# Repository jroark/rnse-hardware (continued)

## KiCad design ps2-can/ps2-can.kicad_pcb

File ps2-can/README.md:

# RNS-E PS/2 to CAN adapter — revision A

Open **ps2-can.kicad_pro** in KiCad 10. This project contains an editable schematic,
a 65 × 45 mm two-layer PCB and local libraries. All parts mount on the top side.
The design is a prototype: it has not been fabricated or electrically tested.
Adapter firmware and the RNS-E Linux CAN/input driver are not included.

## Connections

| Connector | Pin | Signal |
|---|---|---|
| J1 vehicle, numbered square pad first | 1 | Switched +12 V |
| J1 | 2 | Ground |
| J1 | 3 | Infotainment CANH |
| J1 | 4 | Infotainment CANL |
| J2 keyboard / J3 mouse | 1 | PS/2 data |
| J2 / J3 | 2, 6 | Unconnected |
| J2 / J3 | 3 | Ground |
| J2 / J3 | 4 | Individually fused +5 V |
| J2 / J3 | 5 | PS/2 clock |
| J4 UPDI | 1 | +5 V target voltage reference |
| J4 | 2 | UPDI / PA0 |
| J4 | 3 | Ground |

J4 is a **5 V UPDI** connection. Power the target from J1; configure the programmer
to sense target voltage without supplying it. Preserve PA0's UPDI fuse setting.
The peripheral sockets are for genuine PS/2 devices; passive USB adapters require
peripherals that explicitly support PS/2. Connect peripherals with power off.
The board shares ground with the vehicle; it is not isolated.

## Ordering

Use [the current stock update](ordering/stock-update.md) for revised headerless
DigiKey and Mouser orders. The base [distributor order files](ordering/README.md)
record the design-MPN baseline for one-board DigiKey or
Mouser upload. They group the BOM into 24 lines / 48 components, excluding bare
test pads. The checked BOM corrects the F1 fuse and Y1 crystal package selections
and uses an orderable Vishay SS16 for D1; the existing PCB fits these parts.

## Assembly

Use `bom.csv` for exact MPNs and search links; `previews/assembly.pdf` identifies
parts. Purchase MD-60S sockets made **after 2022-03-03**. Earlier versions have
different hole spacing. The custom footprint follows the current top-view drawing:
pins 4/2/1/3 at x = -3.4/-1.3/+1.3/+3.4 mm, y = 8.5 mm from the front;
pins 6/5 at x = -3.4/+3.4 mm, y = 11 mm; locating slot 2.2 × 0.7 mm at y = 4.7 mm.
Confirm the supplied socket against a 1:1 print before soldering.

Fit resistors/capacitors and SOIC devices first, then power protection, LEDs,
crystal, regulator and connectors. Use flux and an ordinary fine soldering tip.
The SOD-323 ESD diodes are the smallest parts; they have exposed terminals and
are bidirectional, so either orientation works. D1/D2 and LEDs are polarized:
follow the cathode marks and assembly drawing. SOIC pin 1 uses the dot/notch.
TP1–TP4 are bare plated holes, not purchased components. H1–H4 accept M2 hardware.
Allow clearance under the board for the mini-DIN locating tabs and solder joints.

## Power and CAN design

J1 input passes through a 0.5 A fuse and SS16 reverse-polarity diode. SMBJ18A
clamps the protected VBAT rail. TSR 1-2450 converts it to 5 V with a 1 A rating.
Input operation is nominally 9–16 V; brownout/reset during cranking is acceptable.
C5 is rated 50 V; the regulator input limit is 36 V and TJA1055 BAT limit is 40 V.
The TVS nominal maximum clamp is 29.2 V at its specified pulse current, below both
limits. This comparison does not establish load-dump immunity: fuse opening time,
TVS energy, source impedance and wiring overshoot need physical testing. Do not
use a continuously applied supply above the TVS stand-off rating.

Each PS/2 port has a 0.20 A hold PTC (temperature dependent). Budget 100 mA each
for keyboard and mouse and approximately 100 mA for board/CAN operation. The
regulator has margin for startup and CAN activity, but these ports are not intended
for illuminated high-current peripherals. Routing uses 0.25 mm tracks with 0.1874 mm fanout sections,
0.20 mm clearances and 0.6/0.3 mm vias. The project minimum trace width is 0.15 mm;
see the PCB width audit for actual widths. Both copper layers have grounded pours; no assumption of automotive EMC
qualification is made.

The bus interface is **TJA1055T**, fault-tolerant ISO 11898-3. A TJA1051, MCP2551,
SN65HVD230 or conventional high-speed CAN module is not a substitute. The MCP2515
is the CAN protocol controller; its 16 MHz crystal supplies the accurate CAN clock.
The AVR uses its internal clock. No CAN FD is used.

R13/R14 provide distributed termination to TJA1055 RTH/RTL, initially 5.6 kΩ each.
They are not a 120 Ω termination across CANH/CANL. NXP recommends a whole-network
effective termination of approximately 100 Ω per line; actual node resistors and
network topology determine the result. The fitted values minimally load an
existing vehicle network. For a small bench network, inspect the other node's
termination and select an appropriate pair (within the manufacturer's limits),
then verify bus levels and error counters. Do not expect a two-node bench with
two 5.6 kΩ terminations to represent a correctly terminated vehicle network.

CAN EN/STB have pull-downs, so the board powers up in standby. TXD has a pull-up;
MCP2515 CS and RESET are pulled high. INH is intentionally unconnected. WAKE is
held to protected VBAT through 10 kΩ. This revision uses switched power; it does
not implement an always-on wake/power manager.

## Firmware interfaces and bring-up

See `firmware-interface.md` for the pin allocation and proposed wire protocol.
The Linux configuration in this repository has evdev but no networking; CAN and
input integration are additional work, not provided by this circuit.

1. Inspect soldering and resistance between VBAT/5 V and ground with power off.
2. With peripherals and vehicle CAN disconnected, apply a current-limited 12 V
   bench supply (start at 100 mA). Check VBAT polarity, 5 V regulation and POWER LED.
3. Attach a 5 V UPDI programmer to J4. Read device identity before programming.
   Start with transceiver EN/STB low; check both with a meter or logic analyzer.
4. Test each PS/2 device separately. Verify idle-high clock/data, reset/BAT exchange,
   open-drain host signaling and independent port fuses. Increase supply current
   limit only as required for the measured peripheral load.
5. Test MCP2515 SPI identity/configuration and internal loopback before enabling
   the transceiver. Check oscillator startup and the selected CAN timing.
6. Connect a correctly terminated **fault-tolerant** CAN bench node and a common
   ground. Start with receive-only operation. Verify ACKs, error counters, bus
   voltage levels and 100 kbit/s timing before transmitting test input packets.
7. Validate CAN identifiers against the actual vehicle network before installation.
   Use bounded packet rates and disable transmission on bus-off or firmware faults.
8. Before any RNS-E hardware test payload is delivered, verify the actual physical
   display-open motor command and separate disc-eject command on normal/error
   screens and during reads/initialization. Keep polling responsive and audit any
   loader/updater handoff. A reset, return shortcut or displayed eject button is
   not proof of physical ejection. This PCB does not replace that control path.

## Files and reproduction

- `ps2-can.kicad_sch`, `.kicad_pcb`, `.kicad_pro`: editable source.
- `ps2-can.kicad_sym`, `ps2-can.pretty/`, library tables: local symbols/footprints.
- `bom.csv`, `connectivity.json`: purchase list and reference connectivity/placement.
- `previews/`: schematic, assembly and board previews.
- `manufacturing/`: Gerbers and Excellon drills for 2 layers, 1.6 mm FR-4, 1 oz copper.
- `reports/`: ERC, DRC, exported schematic netlist and connectivity/width audits.
- `generate.py`: regenerates schematic and **unrouted** PCB; overwrites manual edits.
- `ps2-can.dsn`, `final.ses`: Specctra interchange for the final route.

Generation uses KiCad's bundled Python with `pcbnew`. Route the DSN with
Freerouting 2.5.0, fanout enabled, automatic neckdown disabled and optimization
disabled; the final session routes every connection. Export the schematic XML
netlist to `reports/schematic.xml` before finishing the board. `finish.py` imports the resulting session and fills the ground
zones. Run `label-board.py` once to place the silkscreen legends, then run checks/export again after any change; do not reuse stale Gerbers.
Project symbols deliberately show actual pin numbers and explicit net labels.

## Manufacturer references

- [ATtiny1616 datasheet](https://ww1.microchip.com/downloads/aemDocuments/documents/MCU08/ProductDocuments/DataSheets/ATtiny1614-16-17-DataSheet-DS40002204A.pdf)
- [MCP2515 datasheet](https://ww1.microchip.com/downloads/en/DeviceDoc/MCP2515-Stand-Alone-CAN-Controller-with-SPI-20001801J.pdf)
- [TJA1055 datasheet](https://www.nxp.com/docs/en/data-sheet/TJA1055.pdf) and [application guidance](https://www.nxp.com/docs/en/application-note/AH0801.pdf)
- [MD-S socket drawing, page 3](https://www.sameskydevices.com/product/resource/md-s.pdf)
- [TSR 1 regulator datasheet](https://www.tracopower.com/sites/default/files/products/datasheets/tsr1_datasheet.pdf)
- [PESD5V0S1BA datasheet](https://assets.nexperia.com/documents/data-sheet/PESD5V0S1BA.pdf)

KiCad-derived local footprints retain their original library provenance and are
covered by the KiCad libraries' CC BY-SA 4.0 license with their exception for
commercial PCB fabrication. No third-party firmware is included.

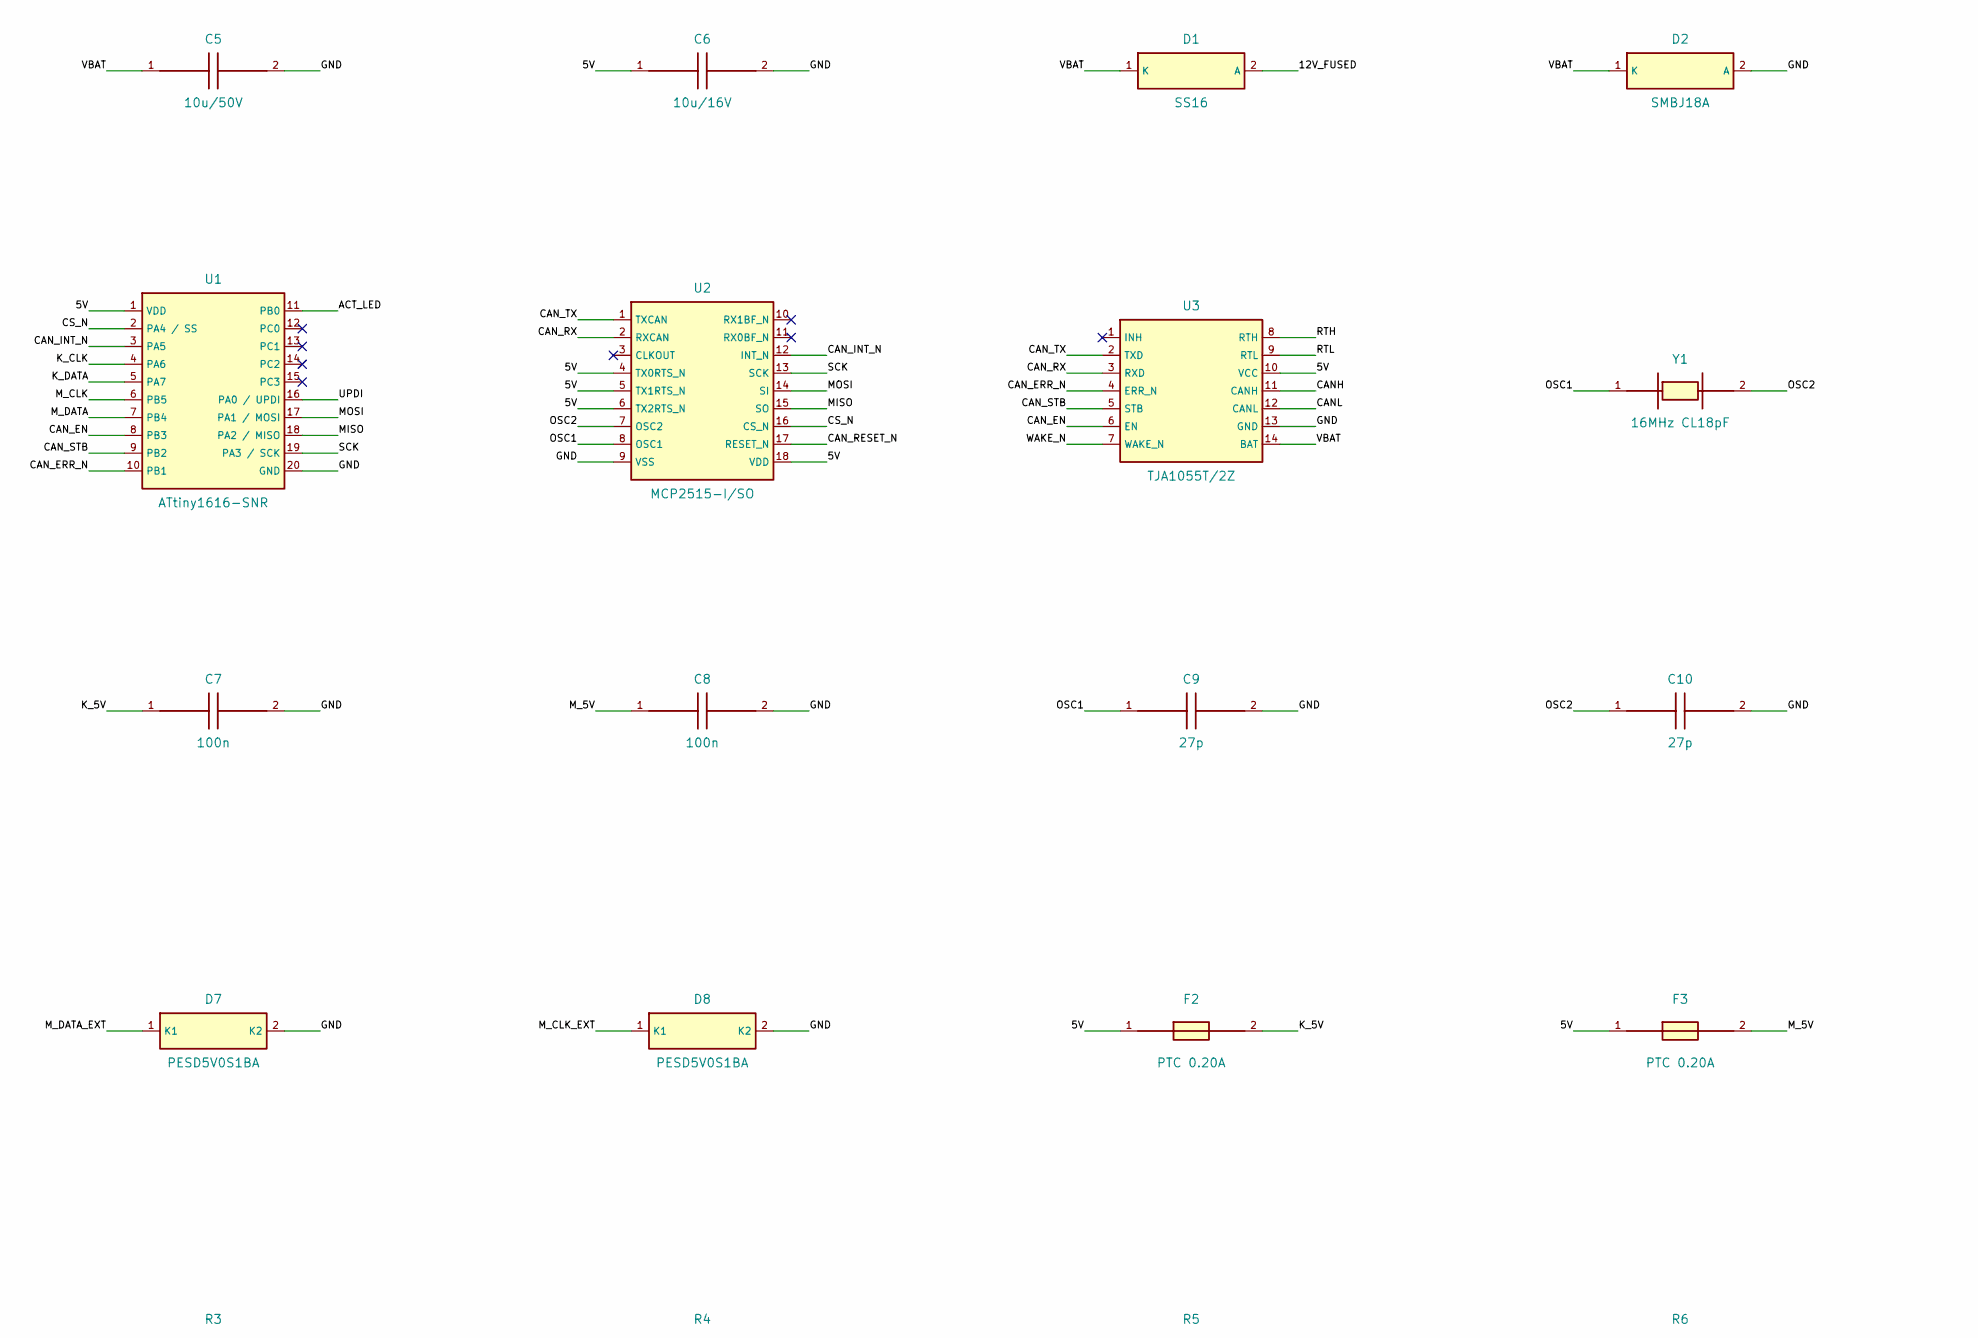
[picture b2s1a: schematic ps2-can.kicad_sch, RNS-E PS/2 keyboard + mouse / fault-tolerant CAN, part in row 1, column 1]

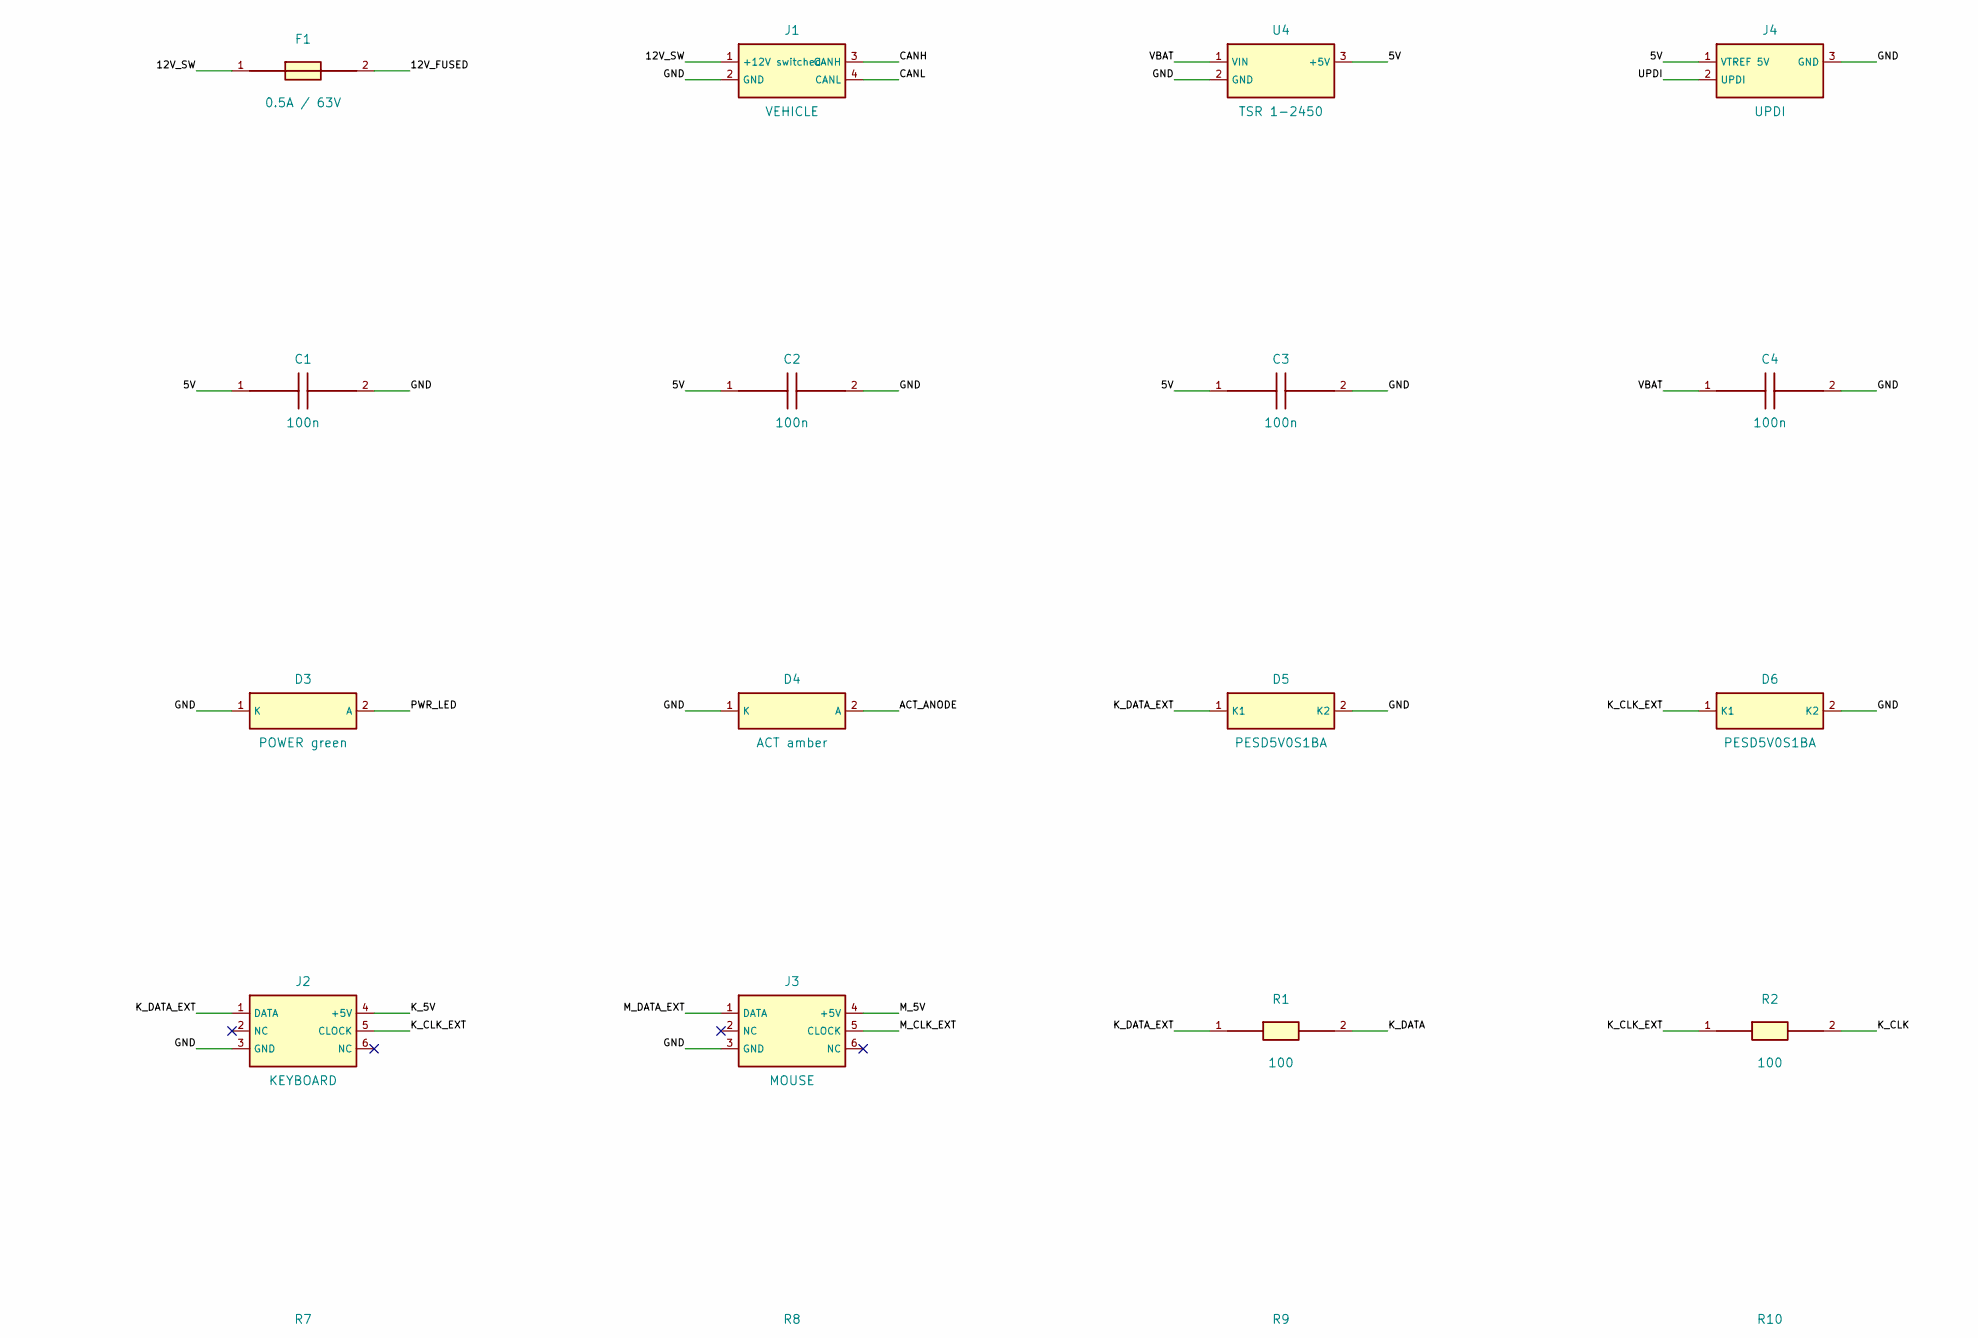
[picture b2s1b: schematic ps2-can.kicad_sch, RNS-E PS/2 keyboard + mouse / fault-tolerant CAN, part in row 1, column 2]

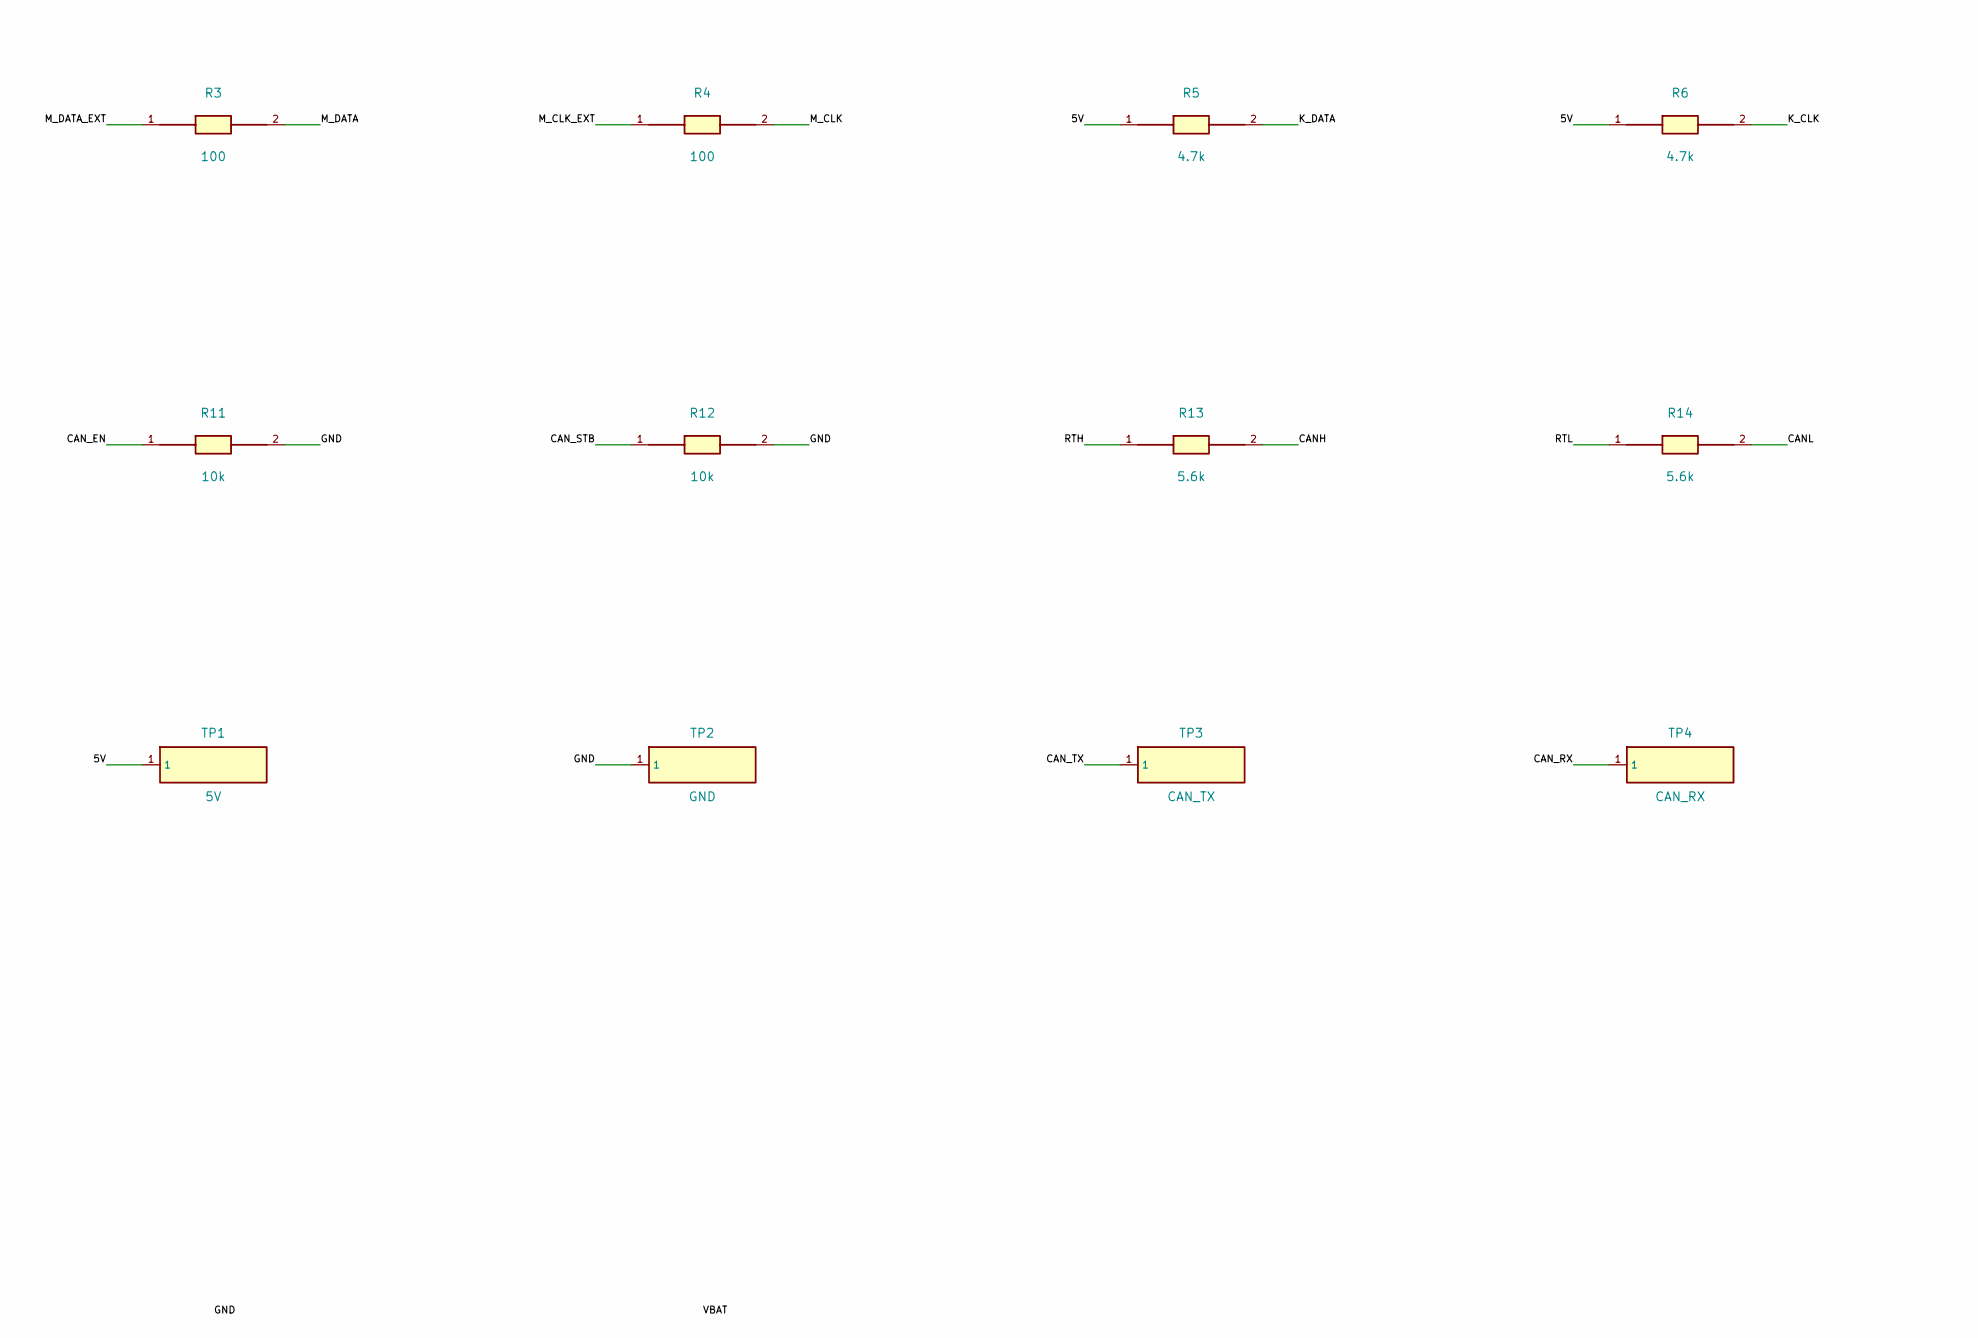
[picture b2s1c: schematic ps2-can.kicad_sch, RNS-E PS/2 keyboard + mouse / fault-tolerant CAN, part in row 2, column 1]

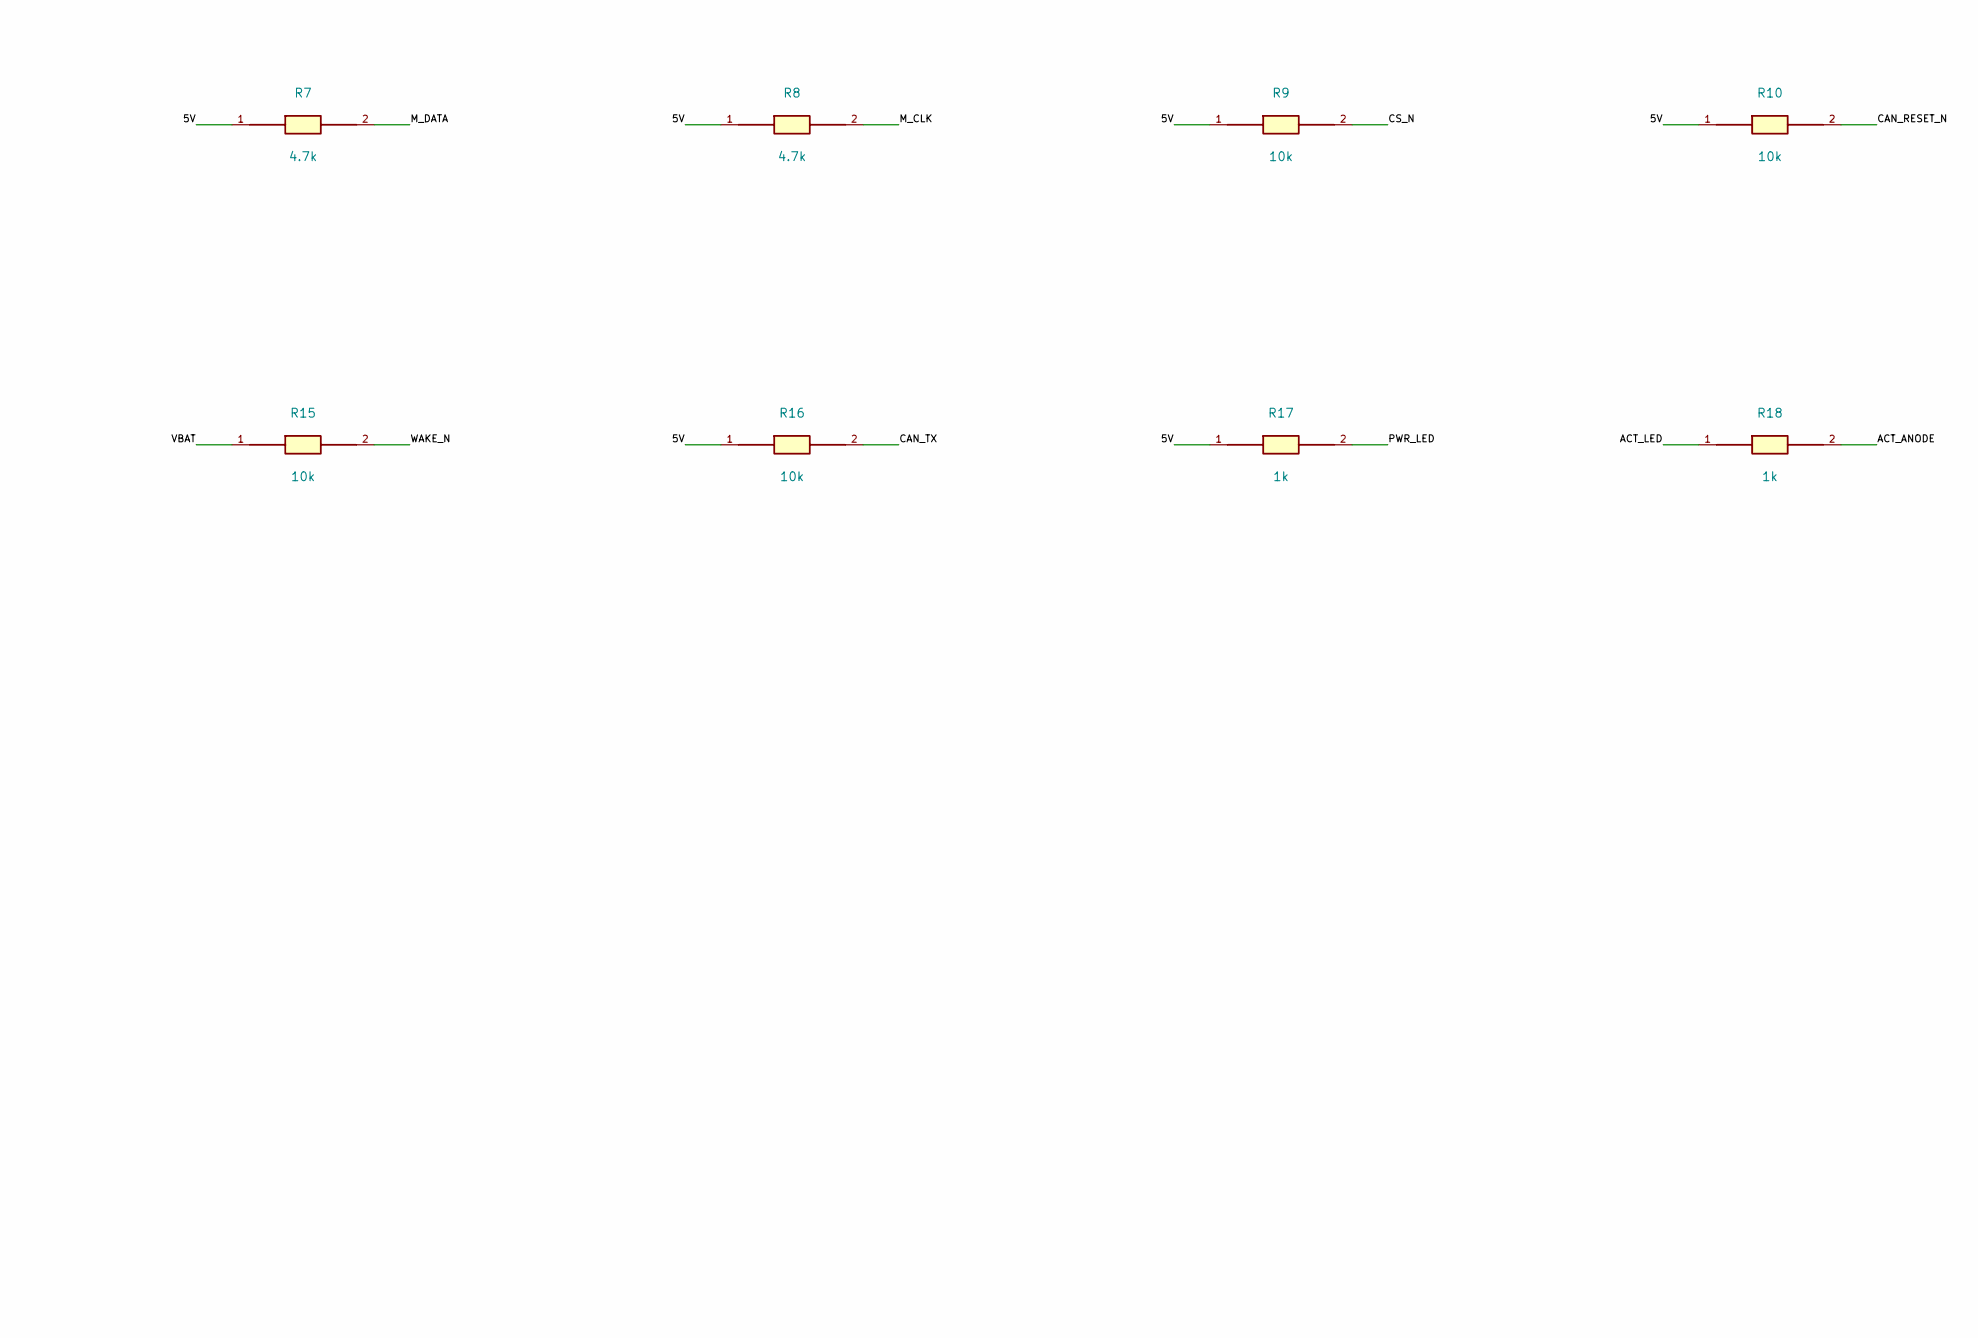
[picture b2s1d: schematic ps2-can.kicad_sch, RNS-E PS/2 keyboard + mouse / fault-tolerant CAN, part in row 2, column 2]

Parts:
C1, C2, C3, C4, C7, C8: 100n; C_0805_2012Metric_Pad1.18x1.45mm_HandSolder
C5: 10u/50V; C_0805_2012Metric_Pad1.18x1.45mm_HandSolder
C6: 10u/16V; C_0805_2012Metric_Pad1.18x1.45mm_HandSolder
C9, C10: 27p; C_0805_2012Metric_Pad1.18x1.45mm_HandSolder
D1: SS16; D_SMA
D2: SMBJ18A; D_SMB
D3: POWER green; LED_0805_2012Metric_Pad1.15x1.40mm_HandSolder
D4: ACT amber; LED_0805_2012Metric_Pad1.15x1.40mm_HandSolder
D5, D6, D7, D8: PESD5V0S1BA; D_SOD-323
F1: 0.5A / 63V; Fuse_1206_3216Metric_Pad1.42x1.75mm_HandSolder
F2, F3: PTC 0.20A; Fuse_1812_4532Metric
J1: VEHICLE; TerminalBlock_Phoenix_MKDS-1,5-4-5.08_1x04_P5.08mm_Horizont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
J2: KEYBOARD; MD-60S_2022
J3: MOUSE; MD-60S_2022
J4: UPDI; PinHeader_1x03_P2.54mm_Vertical
R1, R2, R3, R4: 100; R_0805_2012Metric_Pad1.20x1.40mm_HandSolder
R5, R6, R7, R8: 4.7k; R_0805_2012Metric_Pad1.20x1.40mm_HandSolder
R9, R10, R11, R12, R15, R16: 10k; R_0805_2012Metric_Pad1.20x1.40mm_HandSolder
R13, R14: 5.6k; R_0805_2012Metric_Pad1.20x1.40mm_HandSolder
R17, R18: 1k; R_0805_2012Metric_Pad1.20x1.40mm_HandSolder
TP1: 5V; TestPoint_THTPad_D1.5mm_Drill0.7mm
TP2: GND; TestPoint_THTPad_D1.5mm_Drill0.7mm
TP3: CAN_TX; TestPoint_THTPad_D1.5mm_Drill0.7mm
TP4: CAN_RX; TestPoint_THTPad_D1.5mm_Drill0.7mm
U1: ATtiny1616-SNR; SOIC-20W_7.5x12.8mm_P1.27mm
U2: MCP2515-I/SO; SOIC-18W_7.5x11.6mm_P1.27mm
U3: TJA1055T/2Z; SOIC-14_3.9x8.7mm_P1.27mm
U4: TSR 1-2450; Converter_DCDC_TRACO_TSR-1_THT
Y1: 16MHz CL18pF; Crystal_HC49-4H_Vertical

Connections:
/5V: C1.1, C2.1, C3.1, C6.1, F2.1, F3.1, J4.1 (VTREF 5V), R5.1, R6.1, R7.1, R8.1, R9.1, R10.1, R16.1, R17.1, TP1.1, U1.1 (VDD), U2.4 (TX0RTS_N), U2.5 (TX1RTS_N), U2.6 (TX2RTS_N), U2.18 (VDD), U3.10 (VCC), U4.3 (+5V)
/12V_FUSED: D1.2 (A), F1.2
/12V_SW: F1.1, J1.1 (+12V switched)
/ACT_ANODE: D4.2 (A), R18.2
/ACT_LED: R18.1, U1.11 (PB0)
/CANH: J1.3 (CANH), R13.2, U3.11 (CANH)
/CANL: J1.4 (CANL), R14.2, U3.12 (CANL)
/CAN_EN: R11.1, U1.8 (PB3), U3.6 (EN)
/CAN_ERR_N: U1.10 (PB1), U3.4 (ERR_N)
/CAN_INT_N: U1.3 (PA5), U2.12 (INT_N)
/CAN_RESET_N: R10.2, U2.17 (RESET_N)
/CAN_RX: TP4.1, U2.2 (RXCAN), U3.3 (RXD)
/CAN_STB: R12.1, U1.9 (PB2), U3.5 (STB)
/CAN_TX: R16.2, TP3.1, U2.1 (TXCAN), U3.2 (TXD)
/CS_N: R9.2, U1.2 (PA4 / SS), U2.16 (CS_N)
/GND: C1.2, C2.2, C3.2, C4.2, C5.2, C6.2, C7.2, C8.2, C9.2, C10.2, D2.2 (A), D3.1 (K), D4.1 (K), D5.2 (K2), D6.2 (K2), D7.2 (K2), D8.2 (K2), J1.2 (GND), J2.3 (GND), J3.3 (GND), J4.3 (GND), R11.2, R12.2, TP2.1, U1.20 (GND), U2.9 (VSS), U3.13 (GND), U4.2 (GND)
/K_5V: C7.1, F2.2, J2.4 (+5V)
/K_CLK: R2.2, R6.2, U1.4 (PA6)
/K_CLK_EXT: D6.1 (K1), J2.5 (CLOCK), R2.1
/K_DATA: R1.2, R5.2, U1.5 (PA7)
/K_DATA_EXT: D5.1 (K1), J2.1 (DATA), R1.1
/MISO: U1.18 (PA2 / MISO), U2.15 (SO)
/MOSI: U1.17 (PA1 / MOSI), U2.14 (SI)
/M_5V: C8.1, F3.2, J3.4 (+5V)
/M_CLK: R4.2, R8.2, U1.6 (PB5)
/M_CLK_EXT: D8.1 (K1), J3.5 (CLOCK), R4.1
/M_DATA: R3.2, R7.2, U1.7 (PB4)
/M_DATA_EXT: D7.1 (K1), J3.1 (DATA), R3.1
/OSC1: C9.1, U2.8 (OSC1), Y1.1
/OSC2: C10.1, U2.7 (OSC2), Y1.2
/PWR_LED: D3.2 (A), R17.2
/RTH: R13.1, U3.8 (RTH)
/RTL: R14.1, U3.9 (RTL)
/SCK: U1.19 (PA3 / SCK), U2.13 (SCK)
/UPDI: J4.2 (UPDI), U1.16 (PA0 / UPDI)
/VBAT: C4.1, C5.1, D1.1 (K), D2.1 (K), R15.1, U3.14 (BAT), U4.1 (VIN)
/WAKE_N: R15.2, U3.7 (WAKE_N)

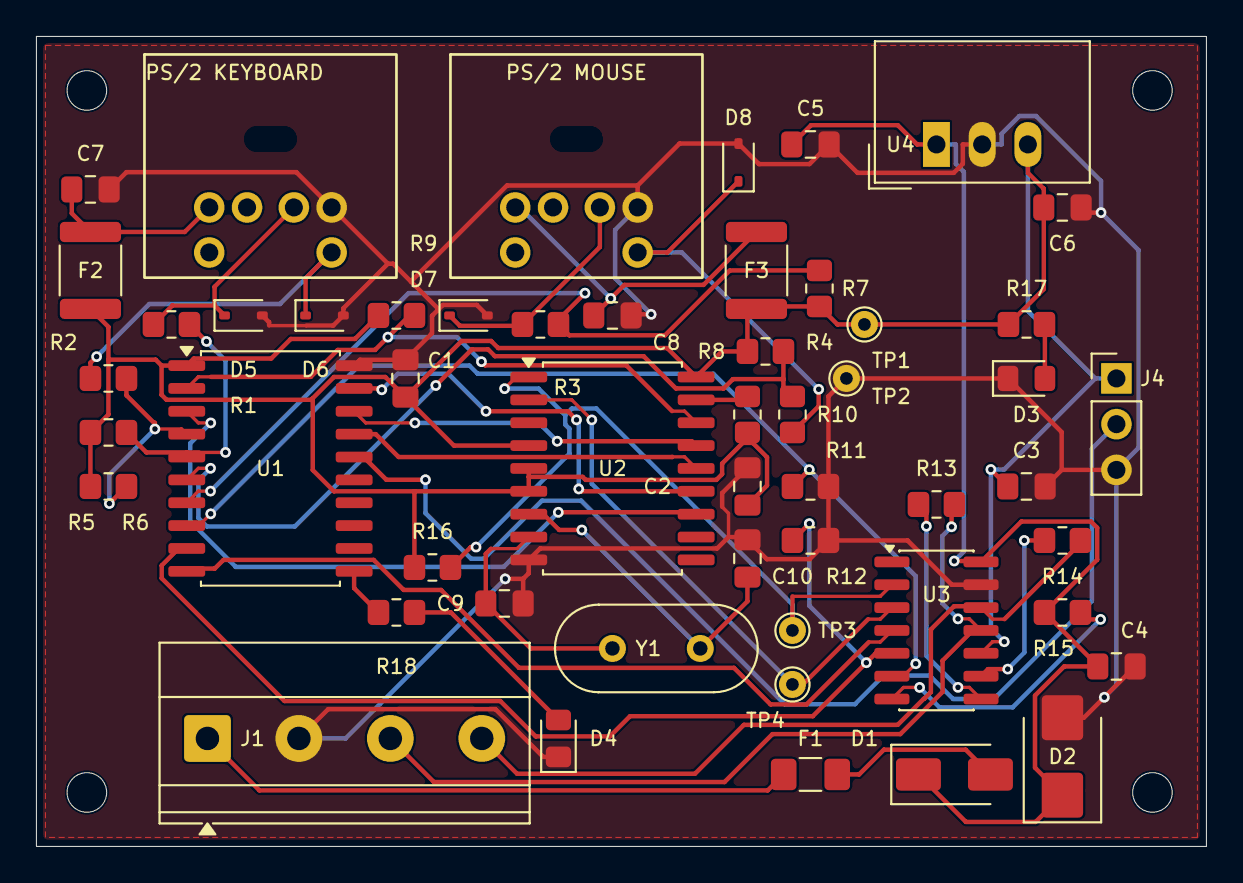
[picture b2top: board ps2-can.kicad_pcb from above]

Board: 2 copper layers, 65.0 x 45.0 mm, 56 parts (0 on the bottom side), 37 nets.

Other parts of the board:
H1, H2, H3, H4: MountingHole_2.2mm_M2

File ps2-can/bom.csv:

Reference,Value,MPN,Footprint,Purchase search,Notes
J1,VEHICLE,1715048,"ps2-can:TerminalBlock_Phoenix_MKDS-1,5-4-5.08_1x04_P5.08mm_Horizontal",https://www.digikey.com/en/products?keywords=1715048,
J2,KEYBOARD,MD-60S,ps2-can:MD-60S_2022,https://www.digikey.com/en/products?keywords=MD-60S,Use date code after 2022-03-03
J3,MOUSE,MD-60S,ps2-can:MD-60S_2022,https://www.digikey.com/en/products?keywords=MD-60S,Use date code after 2022-03-03
J4,UPDI,61300311121,ps2-can:PinHeader_1x03_P2.54mm_Vertical,https://www.digikey.com/en/products?keywords=61300311121,
U1,ATtiny1616-SNR,ATTINY1616-SNR,ps2-can:SOIC-20W_7.5x12.8mm_P1.27mm,https://www.digikey.com/en/products?keywords=ATTINY1616-SNR,
U2,MCP2515-I/SO,MCP2515-I/SO,ps2-can:SOIC-18W_7.5x11.6mm_P1.27mm,https://www.digikey.com/en/products?keywords=MCP2515-I%2FSO,
U3,TJA1055T/2Z,TJA1055T/2Z,ps2-can:SOIC-14_3.9x8.7mm_P1.27mm,https://www.digikey.com/en/products?keywords=TJA1055T%2F2Z,
U4,TSR 1-2450,TSR 1-2450,ps2-can:Converter_DCDC_TRACO_TSR-1_THT,https://www.digikey.com/en/products?keywords=TSR%201-2450,
F1,0.5A / 63V,0466.500NR,ps2-can:Fuse_1206_3216Metric_Pad1.42x1.75mm_HandSolder,https://www.digikey.com/en/products?keywords=0466.500NR,
D1,SS16,SS16-E3/61T,ps2-can:D_SMA,https://www.digikey.com/en/products?keywords=SS16-E3%2F61T,
D2,SMBJ18A,SMBJ18A,ps2-can:D_SMB,https://www.digikey.com/en/products?keywords=SMBJ18A,
F2,PTC 0.20A,1812L020/60DR,ps2-can:Fuse_1812_4532Metric,https://www.digikey.com/en/products?keywords=1812L020%2F60DR,
F3,PTC 0.20A,1812L020/60DR,ps2-can:Fuse_1812_4532Metric,https://www.digikey.com/en/products?keywords=1812L020%2F60DR,
R1,100,RC0805FR-07100RL,ps2-can:R_0805_2012Metric_Pad1.20x1.40mm_HandSolder,https://www.digikey.com/en/products?keywords=RC0805FR-07100RL,
R2,100,RC0805FR-07100RL,ps2-can:R_0805_2012Metric_Pad1.20x1.40mm_HandSolder,https://www.digikey.com/en/products?keywords=RC0805FR-07100RL,
R3,100,RC0805FR-07100RL,ps2-can:R_0805_2012Metric_Pad1.20x1.40mm_HandSolder,https://www.digikey.com/en/products?keywords=RC0805FR-07100RL,
R4,100,RC0805FR-07100RL,ps2-can:R_0805_2012Metric_Pad1.20x1.40mm_HandSolder,https://www.digikey.com/en/products?keywords=RC0805FR-07100RL,
R5,4.7k,RC0805FR-074K7L,ps2-can:R_0805_2012Metric_Pad1.20x1.40mm_HandSolder,https://www.digikey.com/en/products?keywords=RC0805FR-074K7L,
R6,4.7k,RC0805FR-074K7L,ps2-can:R_0805_2012Metric_Pad1.20x1.40mm_HandSolder,https://www.digikey.com/en/products?keywords=RC0805FR-074K7L,
R7,4.7k,RC0805FR-074K7L,ps2-can:R_0805_2012Metric_Pad1.20x1.40mm_HandSolder,https://www.digikey.com/en/products?keywords=RC0805FR-074K7L,
R8,4.7k,RC0805FR-074K7L,ps2-can:R_0805_2012Metric_Pad1.20x1.40mm_HandSolder,https://www.digikey.com/en/products?keywords=RC0805FR-074K7L,
R9,10k,RC0805FR-0710KL,ps2-can:R_0805_2012Metric_Pad1.20x1.40mm_HandSolder,https://www.digikey.com/en/products?keywords=RC0805FR-0710KL,
R10,10k,RC0805FR-0710KL,ps2-can:R_0805_2012Metric_Pad1.20x1.40mm_HandSolder,https://www.digikey.com/en/products?keywords=RC0805FR-0710KL,
R11,10k,RC0805FR-0710KL,ps2-can:R_0805_2012Metric_Pad1.20x1.40mm_HandSolder,https://www.digikey.com/en/products?keywords=RC0805FR-0710KL,
R12,10k,RC0805FR-0710KL,ps2-can:R_0805_2012Metric_Pad1.20x1.40mm_HandSolder,https://www.digikey.com/en/products?keywords=RC0805FR-0710KL,
R13,5.6k,RC0805FR-075K6L,ps2-can:R_0805_2012Metric_Pad1.20x1.40mm_HandSolder,https://www.digikey.com/en/products?keywords=RC0805FR-075K6L,
R14,5.6k,RC0805FR-075K6L,ps2-can:R_0805_2012Metric_Pad1.20x1.40mm_HandSolder,https://www.digikey.com/en/products?keywords=RC0805FR-075K6L,
R15,10k,RC0805FR-0710KL,ps2-can:R_0805_2012Metric_Pad1.20x1.40mm_HandSolder,https://www.digikey.com/en/products?keywords=RC0805FR-0710KL,
R16,10k,RC0805FR-0710KL,ps2-can:R_0805_2012Metric_Pad1.20x1.40mm_HandSolder,https://www.digikey.com/en/products?keywords=RC0805FR-0710KL,
R17,1k,RC0805FR-071KL,ps2-can:R_0805_2012Metric_Pad1.20x1.40mm_HandSolder,https://www.digikey.com/en/products?keywords=RC0805FR-071KL,
R18,1k,RC0805FR-071KL,ps2-can:R_0805_2012Metric_Pad1.20x1.40mm_HandSolder,https://www.digikey.com/en/products?keywords=RC0805FR-071KL,
D3,POWER green,LTST-C170KGKT,ps2-can:LED_0805_2012Metric_Pad1.15x1.40mm_HandSolder,https://www.digikey.com/en/products?keywords=LTST-C170KGKT,
D4,ACT amber,LTST-C170KFKT,ps2-can:LED_0805_2012Metric_Pad1.15x1.40mm_HandSolder,https://www.digikey.com/en/products?keywords=LTST-C170KFKT,
D5,PESD5V0S1BA,"PESD5V0S1BA,115",ps2-can:D_SOD-323,https://www.digikey.com/en/products?keywords=PESD5V0S1BA%2C115,
D6,PESD5V0S1BA,"PESD5V0S1BA,115",ps2-can:D_SOD-323,https://www.digikey.com/en/products?keywords=PESD5V0S1BA%2C115,
D7,PESD5V0S1BA,"PESD5V0S1BA,115",ps2-can:D_SOD-323,https://www.digikey.com/en/products?keywords=PESD5V0S1BA%2C115,
D8,PESD5V0S1BA,"PESD5V0S1BA,115",ps2-can:D_SOD-323,https://www.digikey.com/en/products?keywords=PESD5V0S1BA%2C115,
C1,100n,C0805C104K5RACTU,ps2-can:C_0805_2012Metric_Pad1.18x1.45mm_HandSolder,https://www.digikey.com/en/products?keywords=C0805C104K5RACTU,
C2,100n,C0805C104K5RACTU,ps2-can:C_0805_2012Metric_Pad1.18x1.45mm_HandSolder,https://www.digikey.com/en/products?keywords=C0805C104K5RACTU,
C3,100n,C0805C104K5RACTU,ps2-can:C_0805_2012Metric_Pad1.18x1.45mm_HandSolder,https://www.digikey.com/en/products?keywords=C0805C104K5RACTU,
C4,100n,C0805C104K5RACTU,ps2-can:C_0805_2012Metric_Pad1.18x1.45mm_HandSolder,https://www.digikey.com/en/products?keywords=C0805C104K5RACTU,
C5,10u/50V,GRM21BR61H106KE43L,ps2-can:C_0805_2012Metric_Pad1.18x1.45mm_HandSolder,https://www.digikey.com/en/products?keywords=GRM21BR61H106KE43L,
C6,10u/16V,GRM21BR61C106KE15L,ps2-can:C_0805_2012Metric_Pad1.18x1.45mm_HandSolder,https://www.digikey.com/en/products?keywords=GRM21BR61C106KE15L,
C7,100n,C0805C104K5RACTU,ps2-can:C_0805_2012Metric_Pad1.18x1.45mm_HandSolder,https://www.digikey.com/en/products?keywords=C0805C104K5RACTU,
C8,100n,C0805C104K5RACTU,ps2-can:C_0805_2012Metric_Pad1.18x1.45mm_HandSolder,https://www.digikey.com/en/products?keywords=C0805C104K5RACTU,
Y1,16MHz CL18pF,ABL-16.000MHZ-B2,ps2-can:Crystal_HC49-4H_Vertical,https://www.digikey.com/en/products?keywords=ABL-16.000MHZ-B2,
C9,27p,C0805C270J5GACTU,ps2-can:C_0805_2012Metric_Pad1.18x1.45mm_HandSolder,https://www.digikey.com/en/products?keywords=C0805C270J5GACTU,
C10,27p,C0805C270J5GACTU,ps2-can:C_0805_2012Metric_Pad1.18x1.45mm_HandSolder,https://www.digikey.com/en/products?keywords=C0805C270J5GACTU,
TP1,5V,TEST PAD,ps2-can:TestPoint_THTPad_D1.5mm_Drill0.7mm,https://www.digikey.com/en/products?keywords=TEST%20PAD,Bare plated test pad; do not purchase
TP2,GND,TEST PAD,ps2-can:TestPoint_THTPad_D1.5mm_Drill0.7mm,https://www.digikey.com/en/products?keywords=TEST%20PAD,Bare plated test pad; do not purchase
TP3,CAN_TX,TEST PAD,ps2-can:TestPoint_THTPad_D1.5mm_Drill0.7mm,https://www.digikey.com/en/products?keywords=TEST%20PAD,Bare plated test pad; do not purchase
TP4,CAN_RX,TEST PAD,ps2-can:TestPoint_THTPad_D1.5mm_Drill0.7mm,https://www.digikey.com/en/products?keywords=TEST%20PAD,Bare plated test pad; do not purchase
